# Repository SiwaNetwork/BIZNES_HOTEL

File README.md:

# Модуль спутниковой связи сверхкомпактный — ТЕНШ.464512.001

Справка о возможной реализации модуля спутниковой связи для малоразмерного биогибридного
летательного аппарата (голубя) с бюджетом массы полезной нагрузки 40–60 г.
Стадия — технический проект (проработка). Документы оформлены по ЕСКД.

## Комплект документов (`docs/`)

Основной вариант — модуль L-диапазона (через КА на ГСО):

| Обозначение | Документ | Формат |
|---|---|---|
| ТЕНШ.464512.001 ПЗ | Пояснительная записка (справка о возможной реализации) | А4 |
| ТЕНШ.464512.001 Э1 | Схема электрическая структурная | А3 |
| ТЕНШ.464512.001 Э3 | Схема электрическая принципиальная | А3, 5 л. |
| ТЕНШ.464512.001 ПЭ3 | Перечень элементов | А4 |
| ТЕНШ.464512.001 | Спецификация | А4 |
| ТЕНШ.464512.001 ГЧ | Габаритный чертёж (модуль, антенна, 3D-вид) | А3 |
| ТЕНШ.687281.001 СБ | Плата печатная многослойная. Сборочный чертёж | А3 |

Вариант на готовом модеме Iridium 9603N (SBD, низкая орбита):

| Обозначение | Документ | Формат |
|---|---|---|
| ТЕНШ.464512.002 ПЗ | Пояснительная записка (справка) | А4 |
| ТЕНШ.464512.002 Э3 | Схема электрическая принципиальная | А3 |
| ТЕНШ.464512.002 ПЭ3 | Перечень элементов | А4 |
| ТЕНШ.464512.002 | Спецификация | А4 |
| ТЕНШ.464512.002 ГЧ | Габаритный чертёж | А3 |
| ТЕНШ.758726.002 | Плата печатная (чертёж) | А3 |

## Проекты плат KiCad (`kicad/`)

| Каталог | Плата | Слои | DRC |
|---|---|---|---|
| `TENSH.464512.001` | модуль L-диапазона 32 × 22 мм | 4 | без нарушений |
| `TENSH.464512.002` | носитель модема Iridium 32 × 45 мм | 2 | без нарушений |

В каждом каталоге — схема (`.kicad_sch`), плата (`.kicad_pcb`), библиотеки проекта, отчёт DRC и
производственные файлы `fab/`: Gerber, сверловка, перечень (BOM) и координаты для монтажа (архив `*_gerber.zip`).
Схема и плата строятся из одного списка соединений (`src/hw/*.py`), из него же — Э3, ПЭ3 и спецификация.

## 3D-модель и макет (`cad/`)

- `module.step`, `antenna.step`, `assembly.step` — 3D-модели модуля L-диапазона (STEP AP214, с цветами);
- `module_iridium.step` — 3D-модель варианта Iridium;
- `mockup_module.stl`, `mockup_antenna.stl` — печать массогабаритного макета;
- `renders/*.png` — изометрические виды.

## Ключевые цифры (оценка)

| Параметр | Значение |
|---|---|
| Модуль без корпуса | 32 × 22 × 2,5 мм, 4,0 г (не более 4,5 г) |
| Диапазон | L-диапазон ПСС, ПД 1626,5–1660,5 МГц / ПР 1525–1559 МГц, через КА на ГСО |
| Мощность ПД | 0,1–1 Вт; потребление при ПД 2,2–3,2 Вт (импульсно), приём ≤ 85 мВт, сон ≤ 0,2 мВт |
| Скорость | с борта BPSK 275–600 бит/с при G/T КА 0…+10 дБ/К (через глобальный луч −10 дБ/К канал не замыкается); на борт LoRa 60–590 бит/с при ЭИИМ КА 20–30 дБВт |
| Антенна | керамическая 25 × 25 × 4 мм (10,5 г) или спиральная ⌀12 × 30 мм (5–7 г) |
| Комплект связи | 15,6 г (базовый), 11,1 г (облегчённый) |
| Расход заряда АКБ | 9–115 мА·ч за час полёта (сценарии А–Г) |
| Элементная база | LR2021, GRF5616, BGA524N6, BGS12P2L6, PE64906, SF2236E, TA1926A, ADL5501, STM32L442KC, TPS7A05, TPS22918 |
| Альтернатива | Iridium SBD (ТЕНШ.464512.002) — модем 9603N на плате-носителе, 16,4 г без антенны |

## Сборка

```bash
apt install poppler-utils xvfb kicad openjdk-17-jre   # + Freerouting 1.9 (FREEROUTING_JAR)
pip install reportlab cadquery vtk pillow numpy fonttools
xvfb-run -a python3 src/build.py      # всё, включая 3D и рендеры
python3 src/build.py --no-3d          # только PDF-документы
python3 src/calc.py                   # расчёты радиолинии и энергетики
python3 src/build_hw.py lband         # проект KiCad модуля: схема, плата, трассировка, DRC, Gerber
python3 src/build_hw.py iridium       # то же для платы-носителя Iridium
python3 src/gen_hw_docs.py lband iridium   # Э3, ПЭ3, спецификации
```

Обозначения: код организации ТЕНШ (ГОСТ 2.201). Все значения — расчётные и подлежат
подтверждению макетированием.

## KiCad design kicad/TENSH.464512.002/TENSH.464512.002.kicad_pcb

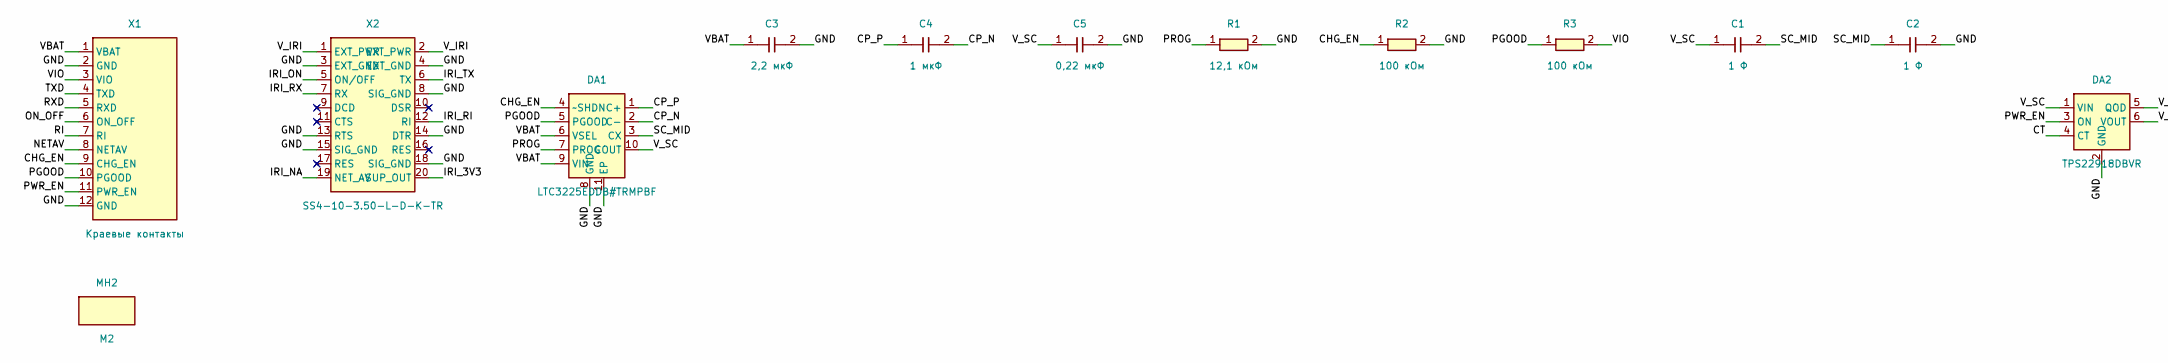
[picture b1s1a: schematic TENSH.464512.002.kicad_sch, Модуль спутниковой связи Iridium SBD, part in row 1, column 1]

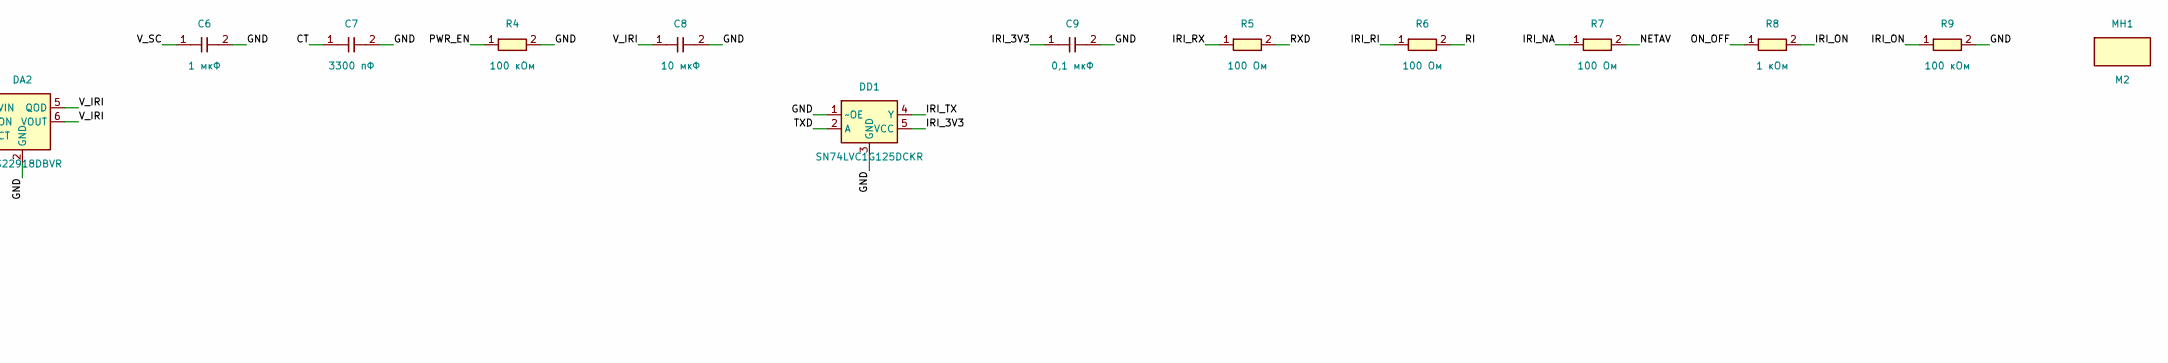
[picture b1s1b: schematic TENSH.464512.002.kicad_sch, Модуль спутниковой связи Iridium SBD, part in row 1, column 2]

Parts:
C1: 1 Ф; SuperCap_Radial_D8.0mm_L13.5mm_Horizontal_L; MPN HV0810-2R7105-R
C2: 1 Ф; SuperCap_Radial_D8.0mm_L13.5mm_Horizontal_R; MPN HV0810-2R7105-R
C3: 2,2 мкФ; C_0603_1608Metric; MPN GRM188R71A225KE15
C4: 1 мкФ; C_0603_1608Metric; MPN GRM188R71C105KA12
C5: 0,22 мкФ; C_0603_1608Metric; MPN GRM188R71A224KA01
C6: 1 мкФ; C_0603_1608Metric; MPN GRM188R71A105KA61
C7: 3300 пФ; C_0402_1005Metric; MPN GRM155R71H332KA01
C8: 10 мкФ; C_0603_1608Metric; MPN GRM188R61A106KE69
C9: 0,1 мкФ; C_0402_1005Metric; MPN GRM155R71C104KA88
DA1: LTC3225EDDB#TRMPBF; DFN-10-1EP_2x3mm_P0.5mm_EP0.64x2.4mm; MPN LTC3225EDDB#TRMPBF
DA2: TPS22918DBVR; SOT-23-6; MPN TPS22918DBVR
DD1: SN74LVC1G125DCKR; SOT-353_SC-70-5; MPN SN74LVC1G125DCKR
MH1, MH2: M2; MountingHole_2.2mm_M2
R1: 12,1 кОм; R_0402_1005Metric; MPN RC0402FR-0712K1L
R2, R3, R4, R9: 100 кОм; R_0402_1005Metric; MPN RC0402FR-07100KL
R5, R6, R7: 100 Ом; R_0402_1005Metric; MPN RC0402FR-07100RL
R8: 1 кОм; R_0402_1005Metric; MPN RC0402FR-071KL
X1: Краевые контакты; Castellated_1x12_P2.54mm_1.2x1.6mm_D0.8mm
X2: SS4-10-3.50-L-D-K-TR; Samtec_SS4-10_P0.4mm_Iridium9603; MPN SS4-10-3.50-L-D-K-TR

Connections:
CHG_EN: DA1.4 (~SHDN), R2.1, X1.9 (CHG_EN)
CP_N: C4.2, DA1.2 (C-)
CP_P: C4.1, DA1.1 (C+)
CT: C7.1, DA2.4 (CT)
GND: C2.2, C3.2, C5.2, C6.2, C7.2, C8.2, C9.2, DA1.8 (GND), DA1.11 (EP), DA2.2 (GND), DD1.1 (~OE), DD1.3 (GND), R1.2, R2.2, R4.2, R9.2, X1.2 (GND), X1.12 (GND), X2.3 (EXT_GND), X2.4 (EXT_GND), X2.8 (SIG_GND), X2.13 (RTS), X2.14 (DTR), X2.15 (SIG_GND), X2.18 (SIG_GND)
IRI_3V3: C9.1, DD1.5 (VCC), X2.20 (SUP_OUT)
IRI_NA: R7.1, X2.19 (NET_AV)
IRI_ON: R8.2, R9.1, X2.5 (ON/OFF)
IRI_RI: R6.1, X2.12 (RI)
IRI_RX: R5.1, X2.7 (RX)
IRI_TX: DD1.4 (Y), X2.6 (TX)
NETAV: R7.2, X1.8 (NETAV)
ON_OFF: R8.1, X1.6 (ON_OFF)
PGOOD: DA1.5 (PGOOD), R3.1, X1.10 (PGOOD)
PROG: DA1.7 (PROG), R1.1
PWR_EN: DA2.3 (ON), R4.1, X1.11 (PWR_EN)
RI: R6.2, X1.7 (RI)
RXD: R5.2, X1.5 (RXD)
SC_MID: C1.2, C2.1, DA1.3 (CX)
TXD: DD1.2 (A), X1.4 (TXD)
VBAT: C3.1, DA1.6 (VSEL), DA1.9 (VIN), X1.1 (VBAT)
VIO: R3.2, X1.3 (VIO)
V_IRI: C8.1, DA2.5 (QOD), DA2.6 (VOUT), X2.1 (EXT_PWR), X2.2 (EXT_PWR)
V_SC: C1.1, C5.1, C6.1, DA1.10 (COUT), DA2.1 (VIN)

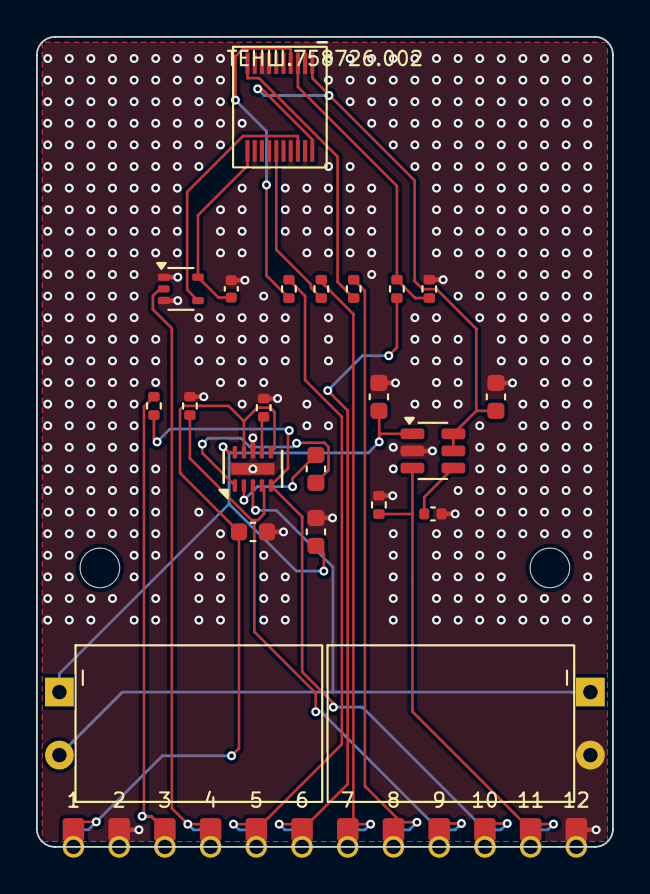
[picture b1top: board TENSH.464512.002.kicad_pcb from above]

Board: 2 copper layers, 32.0 x 45.0 mm, 25 parts (0 on the bottom side), 24 nets.

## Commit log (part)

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2025-09-14 Complete business model system with analytics and web interface
    - Added comprehensive business model calculator for QUANTUM time synchronization project
    - Implemented two monetization models: Equipment Sale + Subscription and Equipment Rental
    - Added support for different assembly options (SHIWA assembled, ETECSA assembly, mixed approach)
    - Created web interface with Flask backend and interactive charts using Chart.js
    - Added detailed financial analytics with tables and visualizations
    - Implemented realistic ROI calculations for hotels (20% instead of unrealistic 33,983%)
2025-10-12 3454
2025-10-12 Исправлено несоответствие в графике работ и добавлены сетевые диаграммы
    - Исправлено дублирование дат 22-24 ноября в technical_plan.md
    - Добавлен раздел обучения персонала (25.11)
    - Создан новый файл network_diagrams.md с полными сетевыми схемами
    - Обновлён README.md с правильными датами и ссылкой на диаграммы
2025-10-12 Удалены упоминания о команде проекта из документации
    - Убраны все упоминания 'команда проекта' и 'проектная команда'
    - Удален раздел 'Команда проекта' из README.md
    - Удален раздел 'Ответственность команды проекта' из technical_plan.md
    - Удален футер с датой подготовки из network_diagrams.md
    - Заменены упоминания в таблице ответственности на 'Ответственные за монтаж'
2025-10-12 Заменен VPN протокол с IPsec/WireGuard на OpenVPN
    - Изменен тип VPN на OpenVPN во всех документах и диаграммах
    - Обновлена конфигурация VPN с параметрами OpenVPN
    - Заменены технические детали IPsec/WireGuard на OpenVPN
    - Обновлены диаграммы безопасности с OpenVPN
2025-10-12 Переименован 'Сервер мониторинга Zabbix + Grafana' в 'SHIWA TIME MONITORING'
    - Во всех документах заменено название системы мониторинга
    - Обновлены все диаграммы с новым названием SHIWA TIME MONITORING
    - Сохранены технические детали о базовых технологиях (Zabbix, Grafana)
    - Обновлены IP-таблицы и конфигурации VPN
2025-10-12 Удален раздел 'Риски и меры mitigации'
    - Убран раздел с рисками отелей, оператора и общими рисками
    - Документ стал более лаконичным и сфокусированным на технических требованиях
2025-10-12 Исправлено размещение грозозащиты (SPD) - теперь на крыше рядом с антенной
    - SPD перенесена из серверной на крышу для эффективной защиты
    - Грозозащита должна отводить импульсные перенапряжения ДО длинного кабеля
    - Обновлены все технические планы и диаграммы
    - Это правильное техническое решение для защиты от грозовых разрядов
2025-10-12 Добавлены тесты с осциллографом и Wireshark для проверки NTP/PTP
    Тестирование с осциллографом: проверка сигнала 1PPS, джиттер, стабильность
    Тестирование NTP в Wireshark: stratum 1, Reference ID GPS/GNSS, анализ пакетов
    Тестирование PTP в Wireshark: Sync, Announce, clockClass=6, multicast 224.0.1.129
    Добавлены инструменты: осциллограф и ноутбук с Wireshark
2025-10-12 Выделенные каналы между офисом и отелями сделаны опциональными
    Система мониторинга может работать через обычный интернет отеля
    ВАРИАНТ А: Выделенный канал 10+ Мбит/с (рекомендуемый)
    ВАРИАНТ Б: Интернет отеля 5+ Мбит/с + OpenVPN (альтернатива)
    Обновлены все документы и диаграммы
2025-10-12 Исправлена ошибка парсинга Mermaid диаграммы
    Проблема: дефисы в тексте узлов конфликтуют с синтаксисом Mermaid
    Решение: добавлены кавычки вокруг текста и заменены скобки на 'на базе'
    Теперь диаграмма архитектуры мониторинга корректно отображается
2025-10-12 Полностью переработана диаграмма мониторинга для совместимости с Mermaid
    Исправления:
    1. Добавлены ID для всех subgraph
    2. Убраны все дефисы из названий и текстов
    3. Добавлены кавычки вокруг всех текстов узлов и связей
    4. Упрощён текст без скобок и спецсимволов
    Теперь диаграмма должна корректно отображаться на GitHub
2025-10-12 Переименована система мониторинга в SHIWA NETWORK MONITORING
    Изменения:
    - SHIWA TIME MONITORING -> SHIWA NETWORK MONITORING во всех документах
    - Zabbix + Grafana -> Timebeat Management Platform
    - Обновлены все диаграммы и спецификации
    - Упрощена диаграмма мониторинга (один компонент вместо трех)
    - Система мониторинга теперь базируется на Timebeat Management Platform
2025-10-12 Переименована платформа мониторинга: Timebeat -> Shiwa Management Platform
    Изменения во всех документах:
    - Timebeat Management Platform -> Shiwa Management Platform
    - Обновлены технические спецификации
    - Обновлены диаграммы и описания оборудования
    Платформа мониторинга теперь называется Shiwa Management Platform
2025-10-12 Исправлена диаграмма резервирования и failover для Mermaid
    Изменения:
    1. Добавлены ID для всех subgraph (scenario1-4)
    2. Все тексты узлов взяты в кавычки
    3. Убраны скобки: ИБП (UPS) -> ИБП UPS
    4. Все тексты на связях в кавычках
    5. Убраны двоеточия и тильды из текстов узлов
2025-10-12 Удалено посещение посольства РФ из плана работ
    - Убрана задача 'Посещение посольства РФ' из 24.11
    - Переименован день: 'Итоговая проверка и посольство' -> 'Итоговая проверка систем'
    - День 24.11 теперь полностью посвящен проверке работы систем
2025-10-12 Убран SNMP, обновлена архитектура мониторинга
    Shiwa Management Platform API вместо SNMP
    Elastic Database вместо PostgreSQL
    Grafana для визуализации данных
    Syslog для логов и событий
    Удалены порты 161 и 162
    Добавлен HTTPS API порт 443
2025-10-12 Удален раздел об инструментах для просмотра диаграмм
2025-10-12 Добавлено обязательное требование публичного IP для SHIWA NETWORK MONITORING
    КРИТИЧЕСКИ ВАЖНО для системы мониторинга:
    - Статический публичный IP для офиса в Гаване
    - NAT к 192.168.100.50 (SHIWA NETWORK MONITORING)
    - Port forwarding: 443 для Grafana, 1194 для OpenVPN
    Использование публичного IP:
    - Удаленный доступ из РФ к системе мониторинга
2025-10-12 Добавлена информация о SHIWA NETWORK как поставщике материалов и PKI
    В документ добавлено:
    - Все материалы и оборудование предоставляет SHIWA NETWORK
    - Инфраструктура PKI предоставляется SHIWA NETWORK
    - CA (Центр сертификации)
    - Сертификаты для OpenVPN сервера и клиентов
    - SSH ключи для безопасного доступа
2025-10-12 Указано, что центральный офис в Гаване предоставляется ETECSA
    Важная информация:
    - Центральный офис мониторинга в Гаване предоставляется оператором ETECSA
    - Офис ETECSA предоставит помещение для серверной стойки 20U
    - ETECSA предоставит публичный IP для SHIWA NETWORK MONITORING
    - Доступ к крыше офиса ETECSA для установки GNSS-антенны
    Обновлены документы: README, technical_plan, pre_installation_requirements
2025-10-12 Исправлены несоответствия и устаревшая информация в документах
    Исправления:
    1. Удален устаревший порт 4161 (SNMP) из firewall правил
    2. В README добавлена информация о SHIWA NETWORK как поставщике
    3. Добавлено, что центральный офис предоставляет ETECSA
    4. Обновлена таблица ответственности с правильными ролями
    5. SHIWA NETWORK вместо 'Ответственные за монтаж'
2025-10-12 Удалено лишнее описание из README.md
2025-10-16 Оптимизирован график работ с 11 до 8 дней
    Ключевые улучшения:
    - Полный цикл монтажа каждого отеля за 1 день
    - Объединены рекогносцировка и монтаж
    - Обучение персонала перенесено на вечер 21.11
    - Сдача работ на 22.11 вместо 25.11
    - Экономия 3 рабочих дней
2025-10-16 Добавлены рабочие встречи с ETECSA на 17-18 ноября
    17.11 - Встреча с ETECSA в Meliá Cohiba (10:00-12:00)
    Согласование технических параметров и публичного IP
    18.11 - Встреча с ETECSA в Hotel Nacional (10:00-12:00)
    Финализация параметров и график работ в офисе
2025-10-16 Исправлен график: встречи с ETECSA на 17.11 в Meliá Internacional
    Ключевые изменения:
    - 16.11: начало монтажа Meliá Internacional
    - 17.11 утро: завершение монтажа (половина дня)
    - 17.11 день: рабочие встречи с ETECSA в отеле Meliá (14:00-18:00)
    - 18.11: переезд в Гавану + Meliá Cohiba
    - 19.11: Hotel Nacional
2025-10-16 Оптимизирован график: проживание в Варадеро с ежедневными выездами в Гавану (08:00 выезд, 21:00 возврат). 15.11 - только прибытие. Рабочий день 08:00-18:00. Расстояние 150 км, 2.5 часа в одну сторону.
2025-10-16 Удалён раздел со спецификациями оборудования из технического плана
2025-10-25 Период монтажа сокращен до 16-21 ноября включительно (6 дней)
    Изменения:
    - 16.11: Meliá Internacional - рекогносцировка + начало монтажа
    - 17.11: Meliá Internacional - завершение + встречи с ETECSA
    - 18.11: Meliá Cohiba - полный цикл
    - 19.11: Hotel Nacional - полный цикл
    - 20.11: Офис ETECSA - рекогносцировка + стойка
2025-10-25 Уточнения по проекту: точность NTP 10 мс, PTP 50 нс; единообразие названий; усиление безопасности (запрет telnet/alt-web, Syslog TLS 6514); корректировка дат тестирования; KPI VPN; артефакты тестов; 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
2025-10-25 Синхронизация плана работ: период монтажа 16-21 ноября, период тестирования этапа 1 16-21 ноября, точность NTP 10 мс, PTP 50 нс
2025-10-25 Удалена дублирующаяся строка периода монтажа в README
2025-10-25 Корректировка графика: все работы завершаются 21 ноября, отлёт 22 ноября; долгосрочное тестирование начинается 23 ноября
2025-10-25 Добавлены критические чек-листы: подготовка к 21 ноября (вечер 20 ноября) и итоговый чек-лист объектов перед сдачей работ
2025-10-26 Исправлена ошибка синтаксиса Mermaid: заменены \\n на <br/> в подписях связей диаграмм
2025-11-09 Plan B and ETECSA requirements
